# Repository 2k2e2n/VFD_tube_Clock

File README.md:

# VFD_tube_Clock
Digital clock using VFD tubes

# Model
[https://3dviewer.net/#model=https://raw.githubusercontent.com/2k2e2n/VFD_tube_Clock/main/readme_assets/VFDclock.glb]()

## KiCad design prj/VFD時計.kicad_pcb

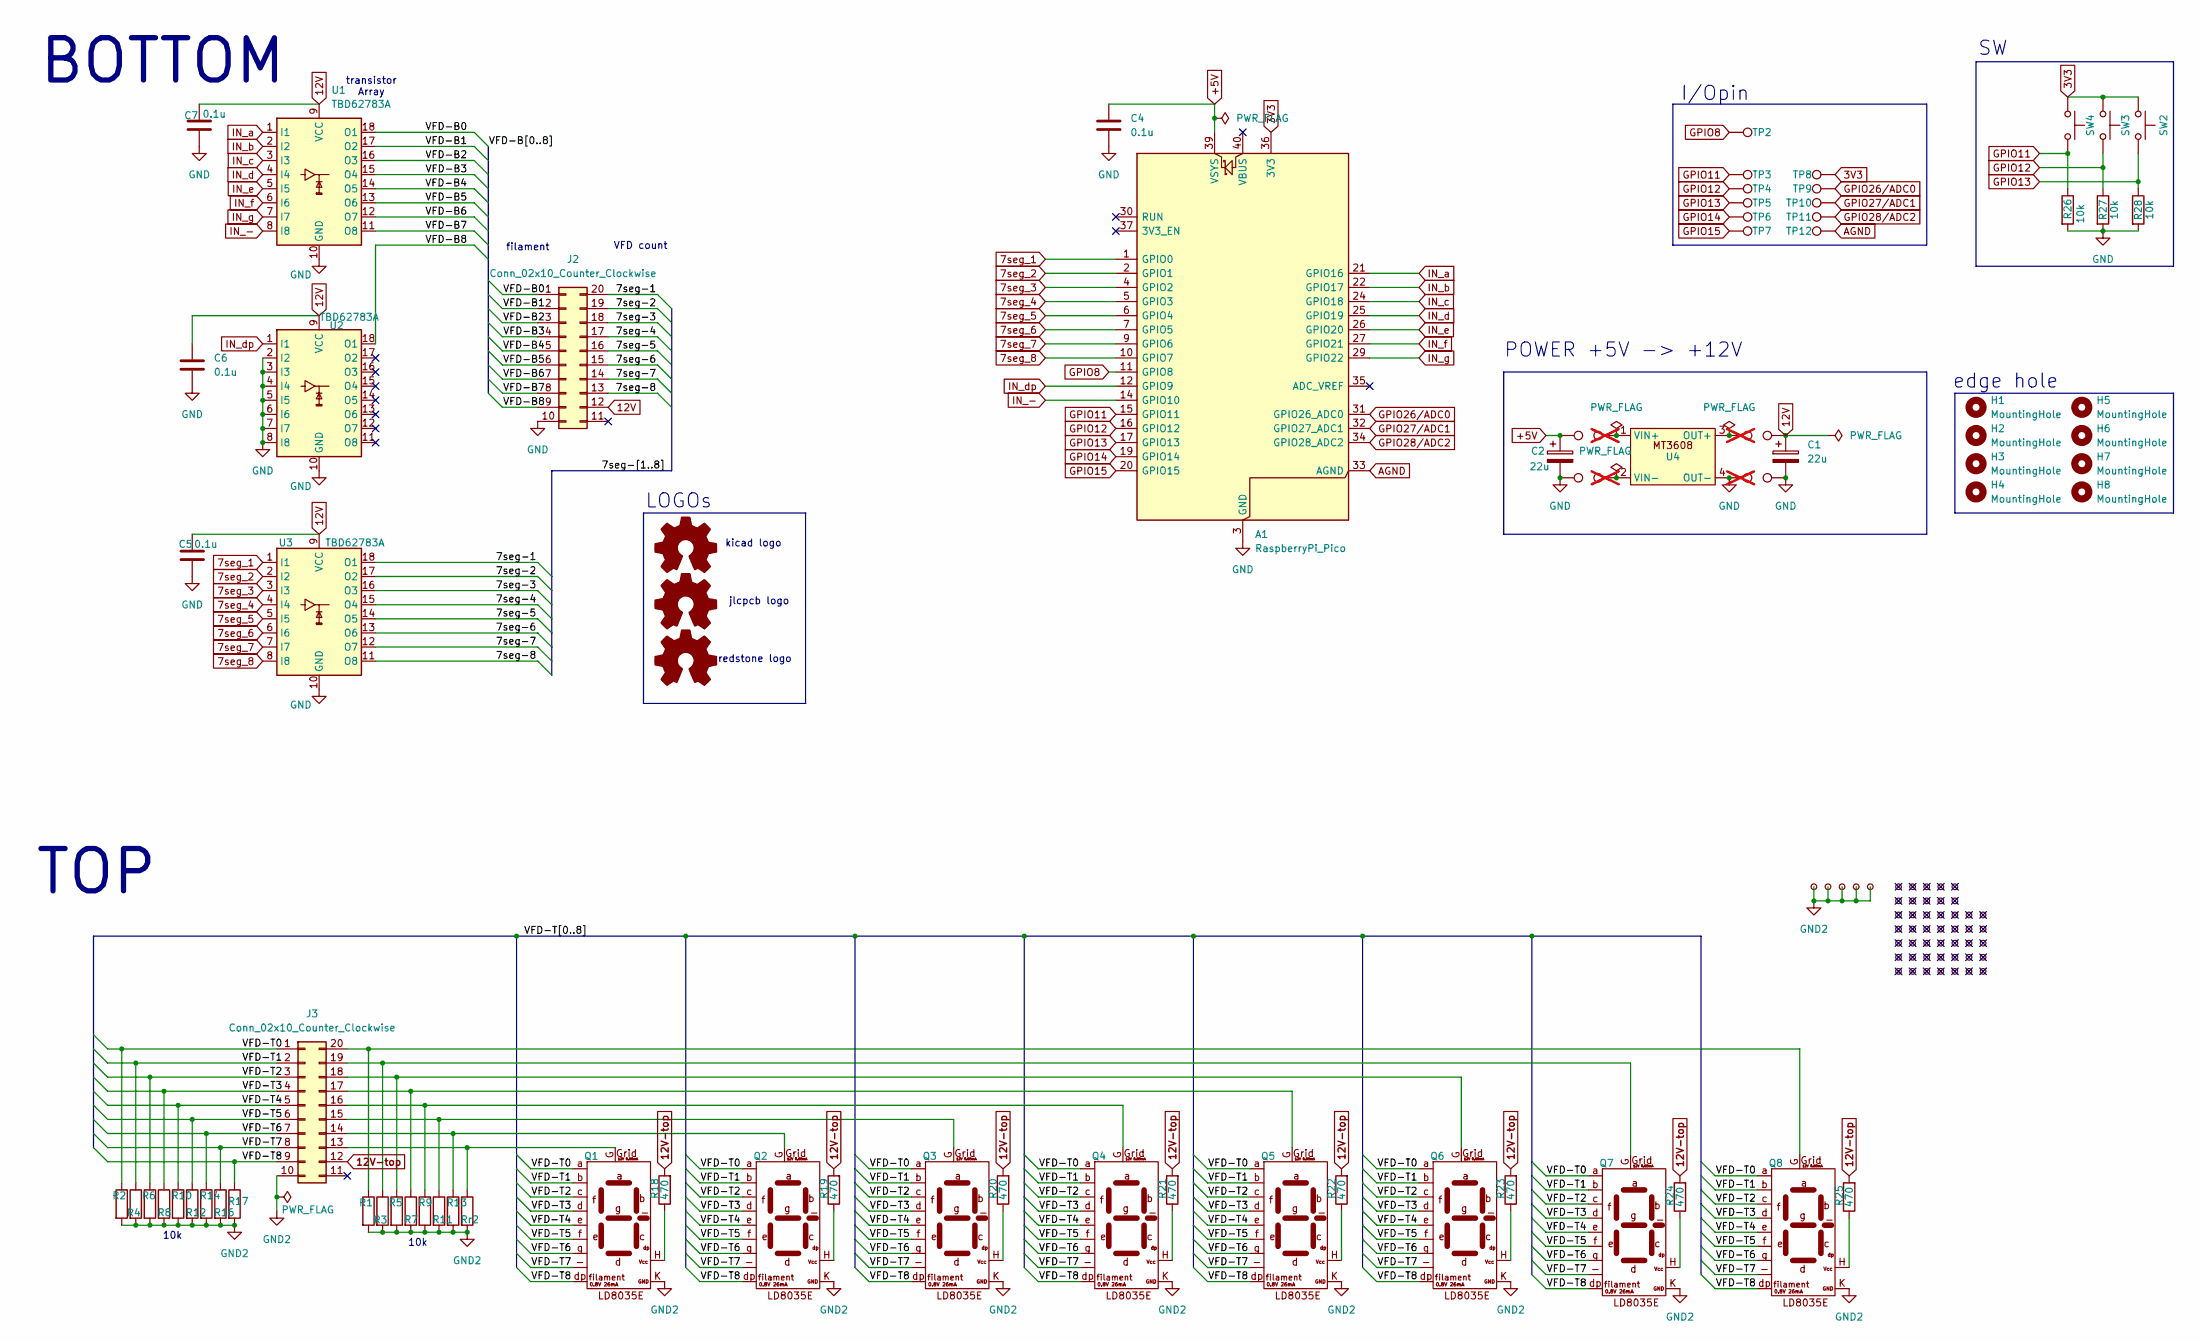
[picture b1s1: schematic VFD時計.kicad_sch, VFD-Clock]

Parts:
A1: RaspberryPi_Pico; RaspberryPi_Pico_Common_Unspecified
C1, C2: 22u; CP_Radial_D6.3mm_P2.50mm
C4, C5, C6, C7: 0.1u; C_Disc_D9.0mm_W2.5mm_P5.00mm
H1, H2, H3, H4, H5, H6, H7, H8: MountingHole; MountingHole_3.2mm_M3
J2, J3: Conn_02x10_Counter_Clockwise; PinSocket_2x10_P2.54mm_Vertical
Q1, Q2, Q3, Q4, Q5, Q6, Q7, Q8: LD8035E
R1, R2, R3, R4, R5, R6, R7, R8, R9, R10, R11, R12, R13, R14, R16, R17, R26, R27, R28: 10k; R_Axial_DIN0207_L6.3mm_D2.5mm_P10.16mm_Horizontal
R18, R19, R20, R21, R22, R23, R24, R25: 470; R_Axial_DIN0207_L6.3mm_D2.5mm_P10.16mm_Horizontal
Rr2: 10k; R_Axial_DIN0207_L6.3mm_D2.5mm_P10.16mm_Horizontal
SW2, SW3, SW4: SW_Push; SW_PUSH_6mm_H7.3mm
TP2, TP3, TP4, TP5, TP6, TP7, TP8, TP9, TP10, TP11, TP12, TP30, TP31, TP34, TP36: TestPoint; TestPoint_THTPad_D2.0mm_Drill1.0mm
TP13, TP14, TP15, TP16, TP17, TP18, TP19, TP20, TP21, TP22, TP23, TP24, TP25, TP26, TP27, TP28, TP37, TP38, TP39, TP40, TP41, TP42, TP43, TP44, TP45, TP46, TP47, TP48, TP49, TP50, TP51, TP52, TP53, TP54, TP55, TP56, TP57, TP58, TP59, TP60, TP61, TP62, TP63, TP64, TP65, TP66, TP67, TP68, TP69, TP70: TestPoint_Small; TestPoint_THTPad_D2.0mm_Drill1.0mm
TP29, TP32, TP33, TP35: TestPoint; TestPoint_THTPad_D2.0mm_Drill1.0mm; not fitted
U1, U2, U3: TBD62783A; CERDIP-18_W7.62mm_SideBrazed_LongPads
U4: MT3608

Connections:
3V3: A1.36 (3V3), SW2.1, SW3.1, SW4.1, TP8.1
7seg_1: A1.1 (GPIO0), U3.1 (I1)
7seg_2: A1.2 (GPIO1), U3.2 (I2)
7seg_3: A1.4 (GPIO2), U3.3 (I3)
7seg_4: A1.5 (GPIO3), U3.4 (I4)
7seg_5: A1.6 (GPIO4), U3.5 (I5)
7seg_6: A1.7 (GPIO5), U3.6 (I6)
7seg_7: A1.9 (GPIO6), U3.7 (I7)
7seg_8: A1.10 (GPIO7), U3.8 (I8)
12V: C1.1, C5.1, C6.1, C7.1, J2.12, TP36.1, U1.9 (VCC), U2.9 (VCC), U3.9 (VCC)
12V-top: J3.12, R18.2, R19.2, R20.2, R21.2, R22.2, R23.2, R24.2, R25.2
+5V: A1.39 (VSYS), C2.1, C4.1, TP30.1
/7seg-1: J2.20, U3.18 (O1)
/7seg-2: J2.19, U3.17 (O2)
/7seg-3: J2.18, U3.16 (O3)
/7seg-4: J2.17, U3.15 (O4)
/7seg-5: J2.16, U3.14 (O5)
/7seg-6: J2.15, U3.13 (O6)
/7seg-7: J2.14, U3.12 (O7)
/7seg-8: J2.13, U3.11 (O8)
/VFD-B0: J2.1, U1.18 (O1)
/VFD-B1: J2.2, U1.17 (O2)
/VFD-B2: J2.3, U1.16 (O3)
/VFD-B3: J2.4, U1.15 (O4)
/VFD-B4: J2.5, U1.14 (O5)
/VFD-B5: J2.6, U1.13 (O6)
/VFD-B6: J2.7, U1.12 (O7)
/VFD-B7: J2.8, U1.11 (O8)
/VFD-B8: J2.9, U2.18 (O1)
/VFD-T0: J3.1, Q1.a, Q2.a, Q3.a, Q4.a, Q5.a, Q6.a, Q7.a, Q8.a, R2.1
/VFD-T1: J3.2, Q1.b, Q2.b, Q3.b, Q4.b, Q5.b, Q6.b, Q7.b, Q8.b, R4.1
/VFD-T2: J3.3, Q1.c, Q2.c, Q3.c, Q4.c, Q5.c, Q6.c, Q7.c, Q8.c, R6.1
/VFD-T3: J3.4, Q1.d, Q2.d, Q3.d, Q4.d, Q5.d, Q6.d, Q7.d, Q8.d, R8.1
/VFD-T4: J3.5, Q1.e, Q2.e, Q3.e, Q4.e, Q5.e, Q6.e, Q7.e, Q8.e, R10.1
/VFD-T5: J3.6, Q1.f, Q2.f, Q3.f, Q4.f, Q5.f, Q6.f, Q7.f, Q8.f, R12.1
/VFD-T6: J3.7, Q1.g, Q2.g, Q3.g, Q4.g, Q5.g, Q6.g, Q7.g, Q8.g, R14.1
/VFD-T7: J3.8, Q1.-, Q2.-, Q3.-, Q4.-, Q5.-, Q6.-, Q7.-, Q8.-, R16.1
/VFD-T8: J3.9, Q1.dp, Q2.dp, Q3.dp, Q4.dp, Q5.dp, Q6.dp, Q7.dp, Q8.dp, R17.1
AGND: A1.33 (AGND), TP12.1
GND: A1.3 (GND), A1.8 (GND), A1.13 (GND), A1.18 (GND), A1.23 (GND), A1.28 (GND), A1.38 (GND), C1.2, C2.2, C4.2, C5.2, C6.2, C7.2, J2.10, R26.2, R27.2, R28.2, TP31.1, TP33.1, TP34.1, U1.10 (GND), U2.2 (I2), U2.3 (I3), U2.4 (I4), U2.5 (I5), U2.6 (I6), U2.7 (I7), U2.8 (I8), U2.10 (GND), U3.10 (GND), U4.4 (OUT-)
GND2: J3.10, Q1.K, Q2.K, Q3.K, Q4.K, Q5.K, Q6.K, Q7.K, Q8.K, R1.2, R2.2, R3.2, R4.2, R5.2, R6.2, R7.2, R8.2, R9.2, R10.2, R11.2, R12.2, R13.2, R14.2, R16.2, R17.2, Rr2.2, TP13.1, TP14.1, TP15.1, TP16.1, TP17.1
GPIO8: A1.11 (GPIO8), TP2.1
GPIO11: A1.15 (GPIO11), R26.1, SW4.2, TP3.1
GPIO12: A1.16 (GPIO12), R27.1, SW3.2, TP4.1
GPIO13: A1.17 (GPIO13), R28.1, SW2.2, TP5.1
GPIO14: A1.19 (GPIO14), TP6.1
GPIO15: A1.20 (GPIO15), TP7.1
GPIO26/ADC0: A1.31 (GPIO26_ADC0), TP9.1
GPIO27/ADC1: A1.32 (GPIO27_ADC1), TP10.1
GPIO28/ADC2: A1.34 (GPIO28_ADC2), TP11.1
IN_-: A1.14 (GPIO10), U1.8 (I8)
IN_a: A1.21 (GPIO16), U1.1 (I1)
IN_b: A1.22 (GPIO17), U1.2 (I2)
IN_c: A1.24 (GPIO18), U1.3 (I3)
IN_d: A1.25 (GPIO19), U1.4 (I4)
IN_dp: A1.12 (GPIO9), U2.1 (I1)
IN_e: A1.26 (GPIO20), U1.5 (I5)
IN_f: A1.27 (GPIO21), U1.6 (I6)
IN_g: A1.29 (GPIO22), U1.7 (I7)
unnamed: J3.13, Q1.G, Rr2.1
unnamed: J3.14, Q2.G, R13.1
unnamed: J3.15, Q3.G, R11.1
unnamed: J3.16, Q4.G, R9.1
unnamed: J3.17, Q5.G, R7.1
unnamed: J3.18, Q6.G, R5.1
unnamed: J3.19, Q7.G, R3.1
unnamed: J3.20, Q8.G, R1.1
unnamed: Q1.H, R18.1
unnamed: Q2.H, R19.1
unnamed: Q3.H, R20.1
unnamed: Q4.H, R21.1
unnamed: Q5.H, R22.1
unnamed: Q6.H, R23.1
unnamed: Q7.H, R24.1
unnamed: Q8.H, R25.1
unnamed: TP29.1, U4.1 (VIN+)
unnamed: TP32.1, U4.2 (VIN-)
unnamed: TP35.1, U4.3 (OUT+)

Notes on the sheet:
I/Opin
transistor Array
10k
TOP
filament
edge hole
VFD count
BOTTOM
POWER +5V -> +12V
jlcpcb logo
kicad logo
redstone logo
LOGOs

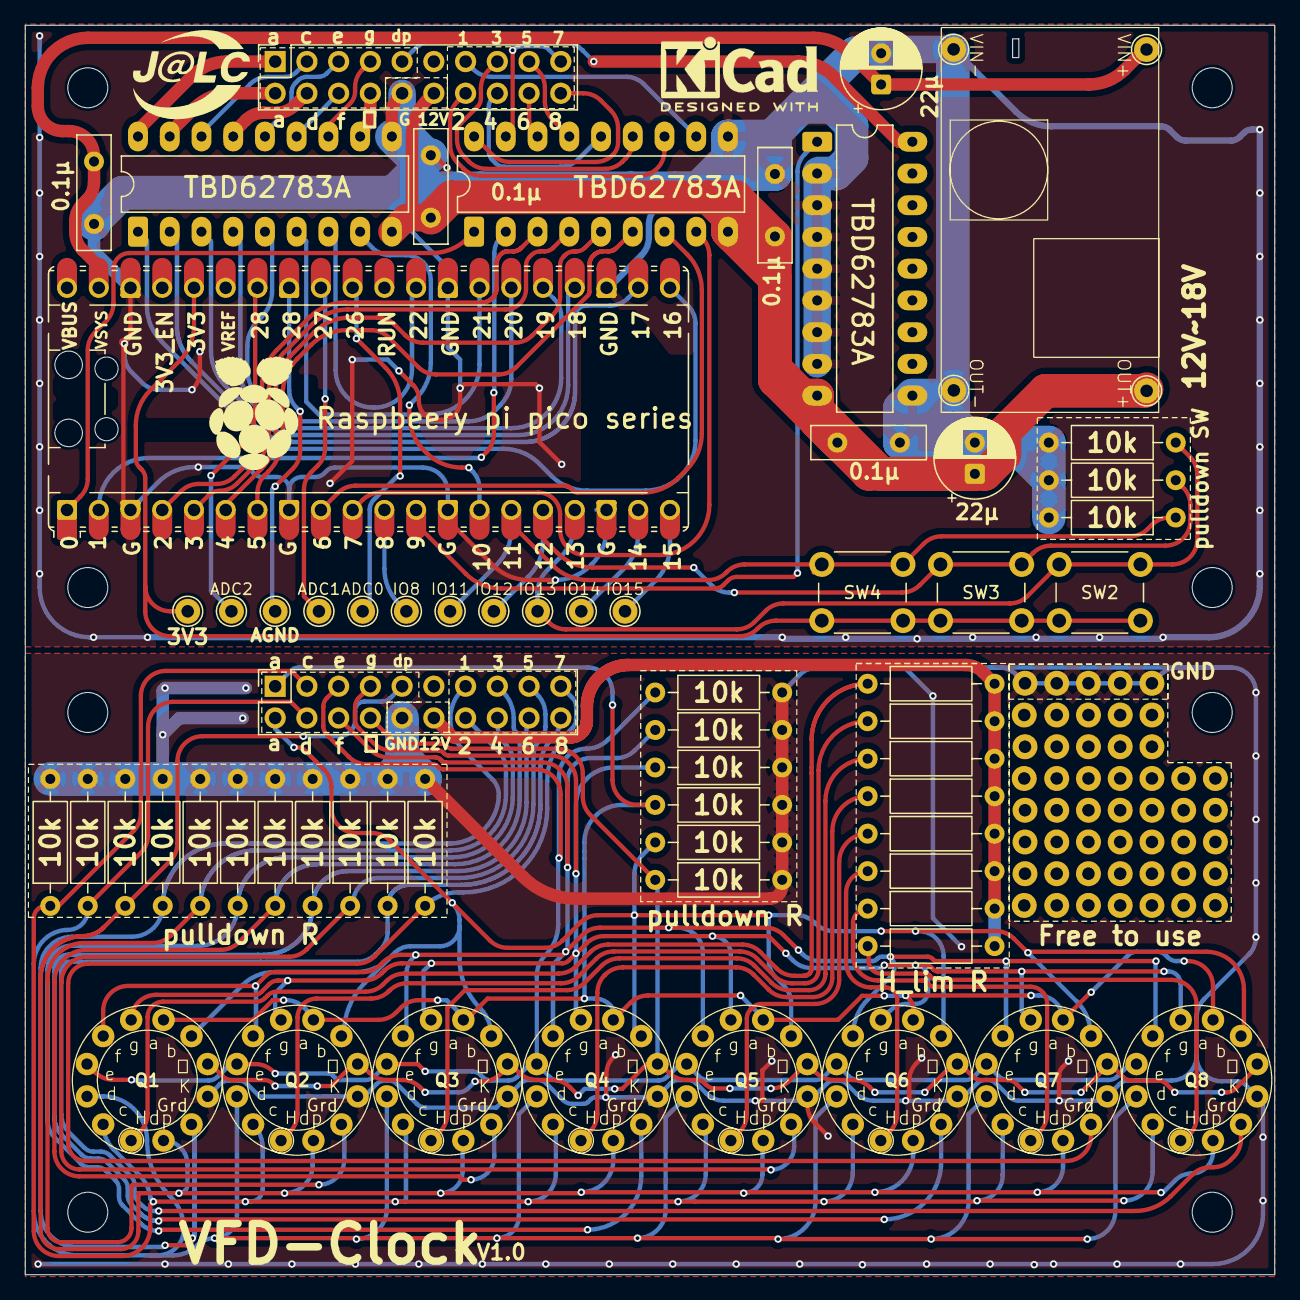
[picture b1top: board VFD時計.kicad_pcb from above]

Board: 2 copper layers, 100.0 x 100.0 mm, 126 parts (0 on the bottom side), 75 nets.

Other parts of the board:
QR*****: QRcode

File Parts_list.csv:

Reference,Qty,Value,DNP,Footprint,Datasheet
A1,1,RaspberryPi_Pico,,Module:RaspberryPi_Pico_Common_Unspecified,https://datasheets.raspberrypi.com/pico/pico-datasheet.pdf
"C1,C2",2,22u,,Capacitor_THT:CP_Radial_D6.3mm_P2.50mm,https://akizukidenshi.com/catalog/g/g117899/
"C4,C5,C6,C7",4,0.1u,,Capacitor_THT:C_Disc_D9.0mm_W2.5mm_P5.00mm,https://akizukidenshi.com/catalog/g/g110147/
"H1,H2,H3,H4,H5,H6,H7,H8",8,MountingHole,,MountingHole:MountingHole_3.2mm_M3,~
"J2,J3",2,Conn_02x10_Counter_Clockwise,,Connector_PinSocket_2.54mm:PinSocket_2x10_P2.54mm_Vertical,"https://akizukidenshi.com/catalog/g/g100078/,https://akizukidenshi.com/catalog/g/g100083/"
"Q1,Q2,Q3,Q4,Q5,Q6,Q7,Q8",8,~,,VFD:LD8035E,https://eleshop.jp/shop/g/g99T416/?srsltid=AfmBOoo7hH0MSEvwu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
"R1,R2,R3,R4,R5,R6,R7,R8,R9,R10,R11,R12,R13,R14,R16,R17,R26,R27,R28,Rr2",20,10k,,Resistor_THT:R_Axial_DIN0207_L6.3mm_D2.5mm_P10.16mm_Horizontal,https://akizukidenshi.com/catalog/g/g125103/
"R18,R19,R20,R21,R22,R23,R24,R25",8,470,,Resistor_THT:R_Axial_DIN0207_L6.3mm_D2.5mm_P10.16mm_Horizontal,https://akizukidenshi.com/catalog/g/g125471/
"SW2,SW3,SW4",3,SW_Push,,Button_Switch_THT:SW_PUSH_6mm_H7.3mm,https://akizukidenshi.com/catalog/g/g103647/
"TP2,TP3,TP4,TP5,TP6,TP7,TP8,TP9,TP10,TP11,TP12,TP30,TP31,TP34,TP36",15,TestPoint,,TestPoint:TestPoint_THTPad_D2.0mm_Drill1.0mm,~
"TP13,TP14,TP15,TP16,TP17,TP18,TP19,TP20,TP21,TP22,TP23,TP24,TP25,TP26,TP27,TP28,TP37,TP38,TP39,TP40,TP41,TP42,TP43,TP44,TP45,TP46,TP47,TP48,TP49,TP50,TP51,TP52,TP53,TP54,TP55,TP56,TP57,TP58,TP59,TP60,TP61,TP62,TP63,TP64,TP65,TP66,TP67,TP68,TP69,TP70",50,TestPoint_Small,,VFD:TestPoint_THTPad_D2.0mm_Drill1.0mm,~
"TP29,TP32,TP33,TP35",4,TestPoint,DNP,TestPoint:TestPoint_THTPad_D2.0mm_Drill1.0mm,~
"U1,U2,U3",3,TBD62783A,,Package_DIP:CERDIP-18_W7.62mm_SideBrazed_LongPads,http://toshiba.semicon-storage.com/info/docget.jsp?did=30523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
U4,1,~,,dcdc-converter:MT3608,https://www.amazon.co.jp/dp/B0CT2SVZFJ?ref=ppx_yo2ov_dt_b_fe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
